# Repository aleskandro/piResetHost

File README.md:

# piResetHost

A basic python daemon for raspberry pi to check an host is down and perform an action to reset the host

It runs on gunicorn and offers a REST API to perform a manual reset.

A checker thread is spawned to ping every 30 seconds the host and perform the reset if it is down.

WARNING: the /reset get request is not secured: it is available to anyone that could reach the server.

### Dependencies:

- python
- gunicorn
- falcon
- python-gpio for Raspberry pi

Tested on TinyCore Linux for RaspberryPi 3.

### To Run

``` gunicorn -b 0.0.0.0:8080 main:api --reload ```

## License

This program is free software: you can redistribute it and/or modify
it under the terms of the GNU General Public License as published by
the Free Software Foundation, either version 3 of the License, or
(at your option) any later version.

This program is distributed in the hope that it will be useful,
but WITHOUT ANY WARRANTY; without even the implied warranty of
MERCHANTABILITY or FITNESS FOR A PARTICULAR PURPOSE.  See the
GNU General Public License for more details.

You should have received a copy of the GNU General Public License
along with this program.  If not, see <http://www.gnu.org/licenses/>.

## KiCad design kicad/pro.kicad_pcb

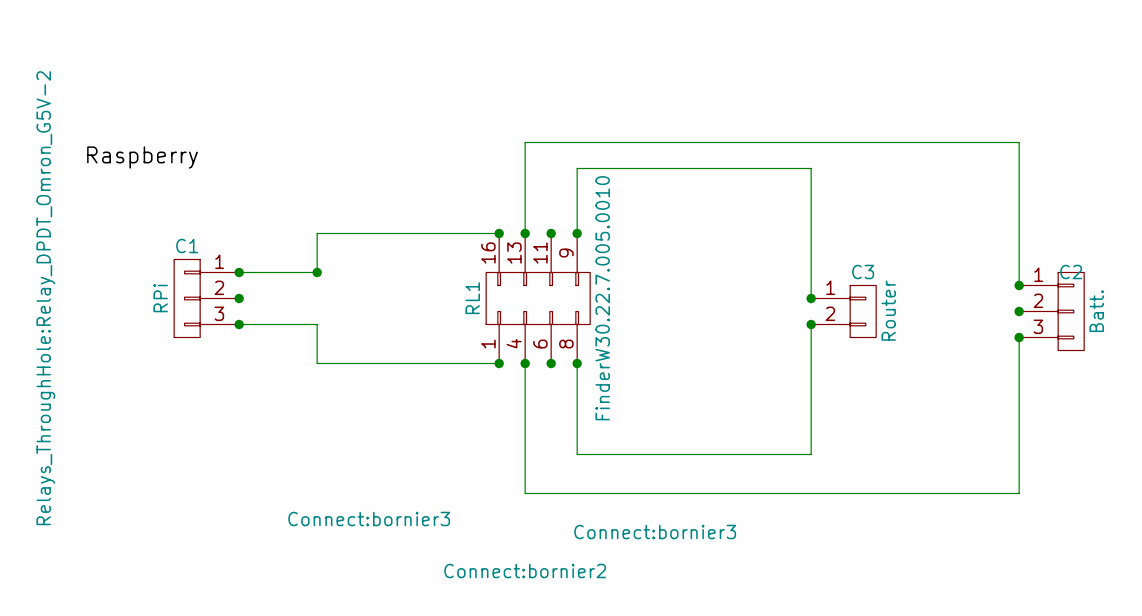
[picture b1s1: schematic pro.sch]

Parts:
C1: RPi; bornier3
C2: Batt.; bornier3
C3: Router; bornier2
RL1: FinderW30.22.7.005.0010; Relay_DPDT_Omron_G5V-2

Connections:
unnamed: C1.1, RL1.16
unnamed: C1.3, RL1.1
unnamed: C2.1, RL1.13
unnamed: C2.3, RL1.4
unnamed: C3.1, RL1.9
unnamed: C3.2, RL1.8

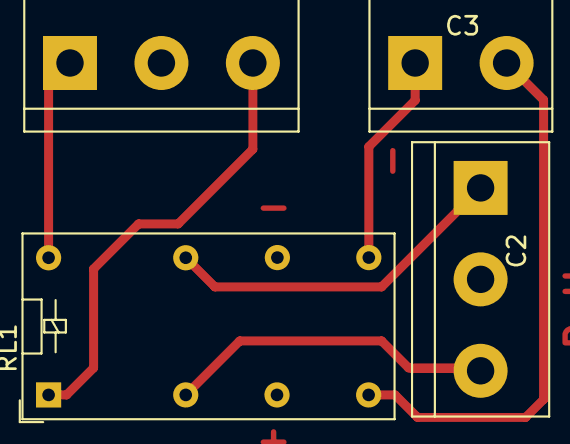
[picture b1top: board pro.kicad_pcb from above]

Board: 2 copper layers, 4 parts (0 on the bottom side), 6 nets.

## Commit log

2017-10-11 Install and run script
2017-10-11 Gitignore
2017-10-11 Ping quiet
2017-10-11 KiCad project
2017-10-18 Missed to change time interval from tests
